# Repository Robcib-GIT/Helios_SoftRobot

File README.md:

**Helios SoftRobot**
=====================================

**Installation and Configuration**
-------------------------------

### Step 1: Clone the Helios repository

Clone the Helios repository using Git:

```bash
git clone https://github.com/JaimeBravoAlgaba/Helios_SoftRobot.git
```

### Step 2: Create a ROS2 workspace

Create a directory for the ROS2 workspace and make sure it's empty:

```bash
mkdir -p helios_ws/src
```

### Step 3: Install the helios_robot package in the workspace

Copy the helios_robot package to the ROS2 workspace:

```bash
cp -r Helios_SoftRobot/Código/helios_robot helios_ws/src
cd helios_ws/src
```

### Step 4: Install the micro_ros_setup package

Clone the micro_ros_setup repository and make sure it's on the branch corresponding to your ROS2 version:

```bash
git clone https://github.com/micro-ROS/micro_ros_setup.git -b $ROS_DISTRO
cd ..
```

### Step 5: Build the workspace

Update dependencies and build the ROS2 workspace:

```bash
rosdep update && rosdep install --from-paths src --ignore-src -y
colcon build --symlink-install
source install/local_setup.bash
```

### Step 6: Create a MicroROS agent

Create a MicroROS agent and configure the environment:

```bash
ros2 run micro_ros_setup create_agent_ws.sh
ros2 run micro_ros_setup build_agent.sh
source install/local_setup.sh
```

### Step 7: Connect to the ESP32 and run the agent

Change your IP address to 192.168.2.76:

Turn on the robot if you haven't already.

**Terminal Control**
-----------
- You can use the helios_robot.sh file to automatically launch the necessary nodes:
```bash
# Launches the MicroROS agent, kinematics and pose prediction
# In the folder where the file is located, run:
./helios_robot.sh
```
and immediately after, click the RESET button on the ESP32.

- Launch the visualization node:
```bash
ros2 run helios_robot helios_robot_plot
```

- Control the cable lengths, in meters:
```bash
# [L00, L01, L02, L03, L10, L11, ... L22, L23]
ros2 topic pub --once /helios_cables_cmd std_msgs/msg/Float32MultiArray "data: [0,0,0,0,  0,0,0,0,  0,0,0,0]"
```

- Send command in theta and phi coordinates, in radians:
```bash
# [th0, th1, th2, phi0, phi1, phi2]
ros2 topic pub --once /helios_sections_cmd std_msgs/msg/Float32MultiArray "data: [0,0,0,  0,0,0]"
```

- Control the tool (value from 0 to 255):
```bash
ros2 topic pub --once /helios_tool_cmd std_msgs/msg/Int8 "data: 127"
```

### Alternative: Connect to ESP32 via USB

You can use the Helios with a USB cable:
Connect the ESP32 to the USB port and upload the esp32 project after uncommenting the lines that allow serial connection in "main.cpp" and changing board_microros_transport to "serial" in the platformio.ini file

Run the MicroROS agent with:

```bash
ros2 run micro_ros_agent micro_ros_agent serial --dev /dev/ttyUSB0
```

### Common Error Resolution

If an error appears when connecting the ESP32, make sure to grant your user access to the ttyUSB0 USB port:

1. Check the user group that has access to the port:
```bash
stat /dev/ttyUSB0
```

It should show something like: "Gid: (   20/ dialout)"

2. Add your user to the "dialout" group or whichever group appeared:
```bash
sudo usermod -a -G dialout $USER
```
3. Grant read and write permissions to the port:
```bash
sudo chmod a+rw /dev/ttyUSB0
```

After resetting the ESP32, its topics should be visible from another terminal.

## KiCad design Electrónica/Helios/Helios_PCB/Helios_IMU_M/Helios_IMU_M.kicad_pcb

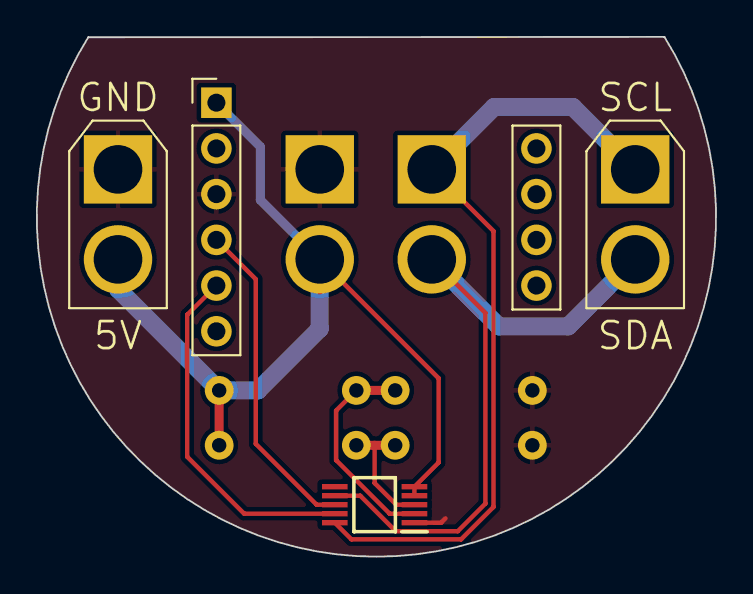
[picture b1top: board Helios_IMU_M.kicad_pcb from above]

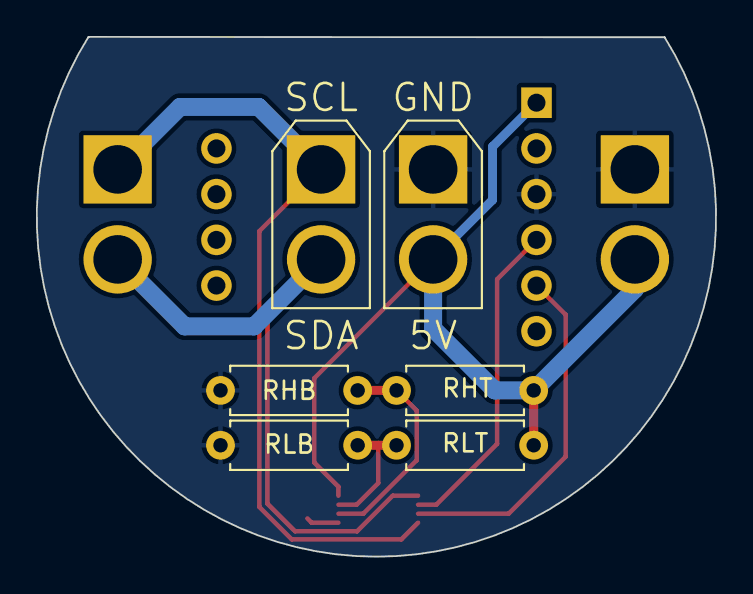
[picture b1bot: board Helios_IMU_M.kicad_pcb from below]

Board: 2 copper layers, 37.7 x 28.9 mm, 10 parts (6 on the bottom side), 8 nets.

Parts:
IMU1: BNO_055
J1, J2, J3, J4: Conn_01x02_Pin; XT30U-M_1x02_P5.0mm_Vertical
LTC4316: LTC4316CMS#PBF; SOP50P490X110-10N
RHB: R; R_Axial_DIN0207_L6.3mm_D2.5mm_P7.62mm_Horizontal
RHT: R; R_Axial_DIN0207_L6.3mm_D2.5mm_P7.62mm_Horizontal
RLB: R; R_Axial_DIN0207_L6.3mm_D2.5mm_P7.62mm_Horizontal
RLT: R; R_Axial_DIN0207_L6.3mm_D2.5mm_P7.62mm_Horizontal

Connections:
GND: IMU1.3 (GND), J1.1, J3.1, LTC4316.1 (GND), RHB.2, RLB.2
SCL: J2.1, J4.1, LTC4316.10 (SCLIN)
SCL_OUT: IMU1.5 (SCL), LTC4316.9 (SCLOUT)
SDA: J2.2, J4.2, LTC4316.7 (SDAIN)
SDA_OUT: IMU1.4 (SDA), LTC4316.8 (SDAOUT)
VCC: IMU1.1 (Vin), J1.2, J3.2, LTC4316.4 (VCC), LTC4316.5 (ENABLE), RHT.1, RLT.1
XORH: LTC4316.2 (XORH), RHB.1, RHT.2
XORL: LTC4316.3 (XORL), RLB.1, RLT.2

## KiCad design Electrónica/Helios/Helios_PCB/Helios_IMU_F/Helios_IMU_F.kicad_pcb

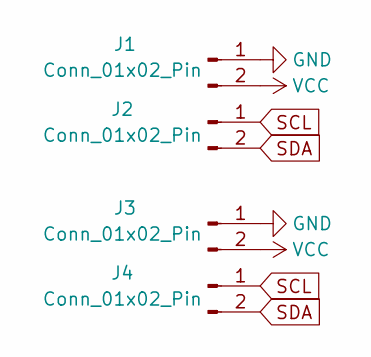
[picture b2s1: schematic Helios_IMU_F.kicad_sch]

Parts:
J1, J2, J3, J4: Conn_01x02_Pin; XT30U-M_1x02_P5.0mm_Vertical

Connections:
GND: J1.1, J3.1
SCL: J2.1, J4.1
SDA: J2.2, J4.2
VCC: J1.2, J3.2

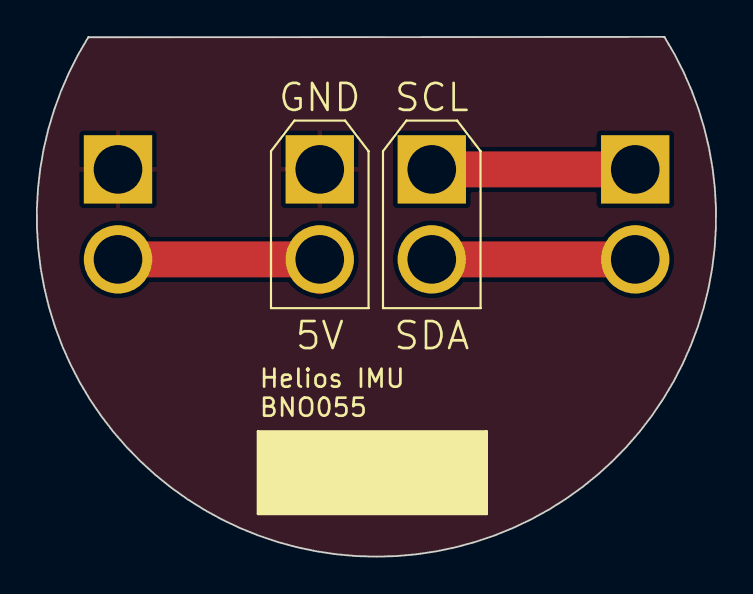
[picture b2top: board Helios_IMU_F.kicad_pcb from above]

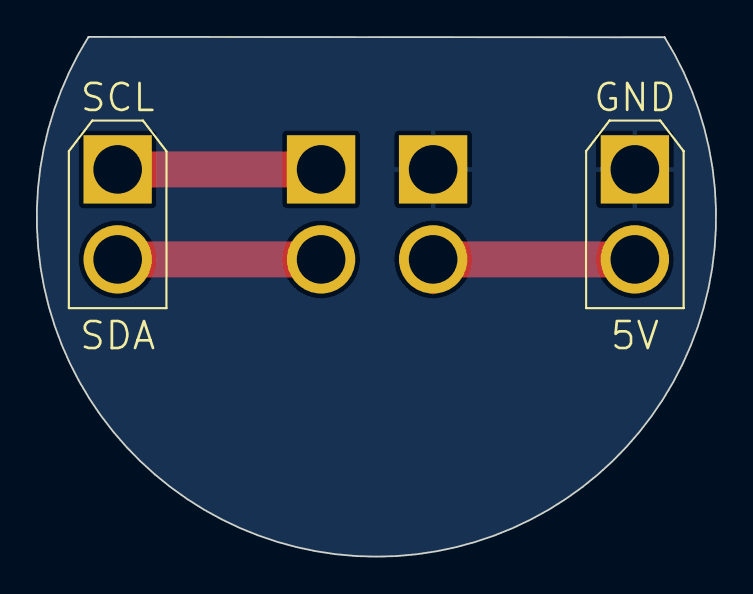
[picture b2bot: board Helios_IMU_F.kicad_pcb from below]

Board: 2 copper layers, 37.7 x 28.9 mm, 4 parts (2 on the bottom side), 4 nets.

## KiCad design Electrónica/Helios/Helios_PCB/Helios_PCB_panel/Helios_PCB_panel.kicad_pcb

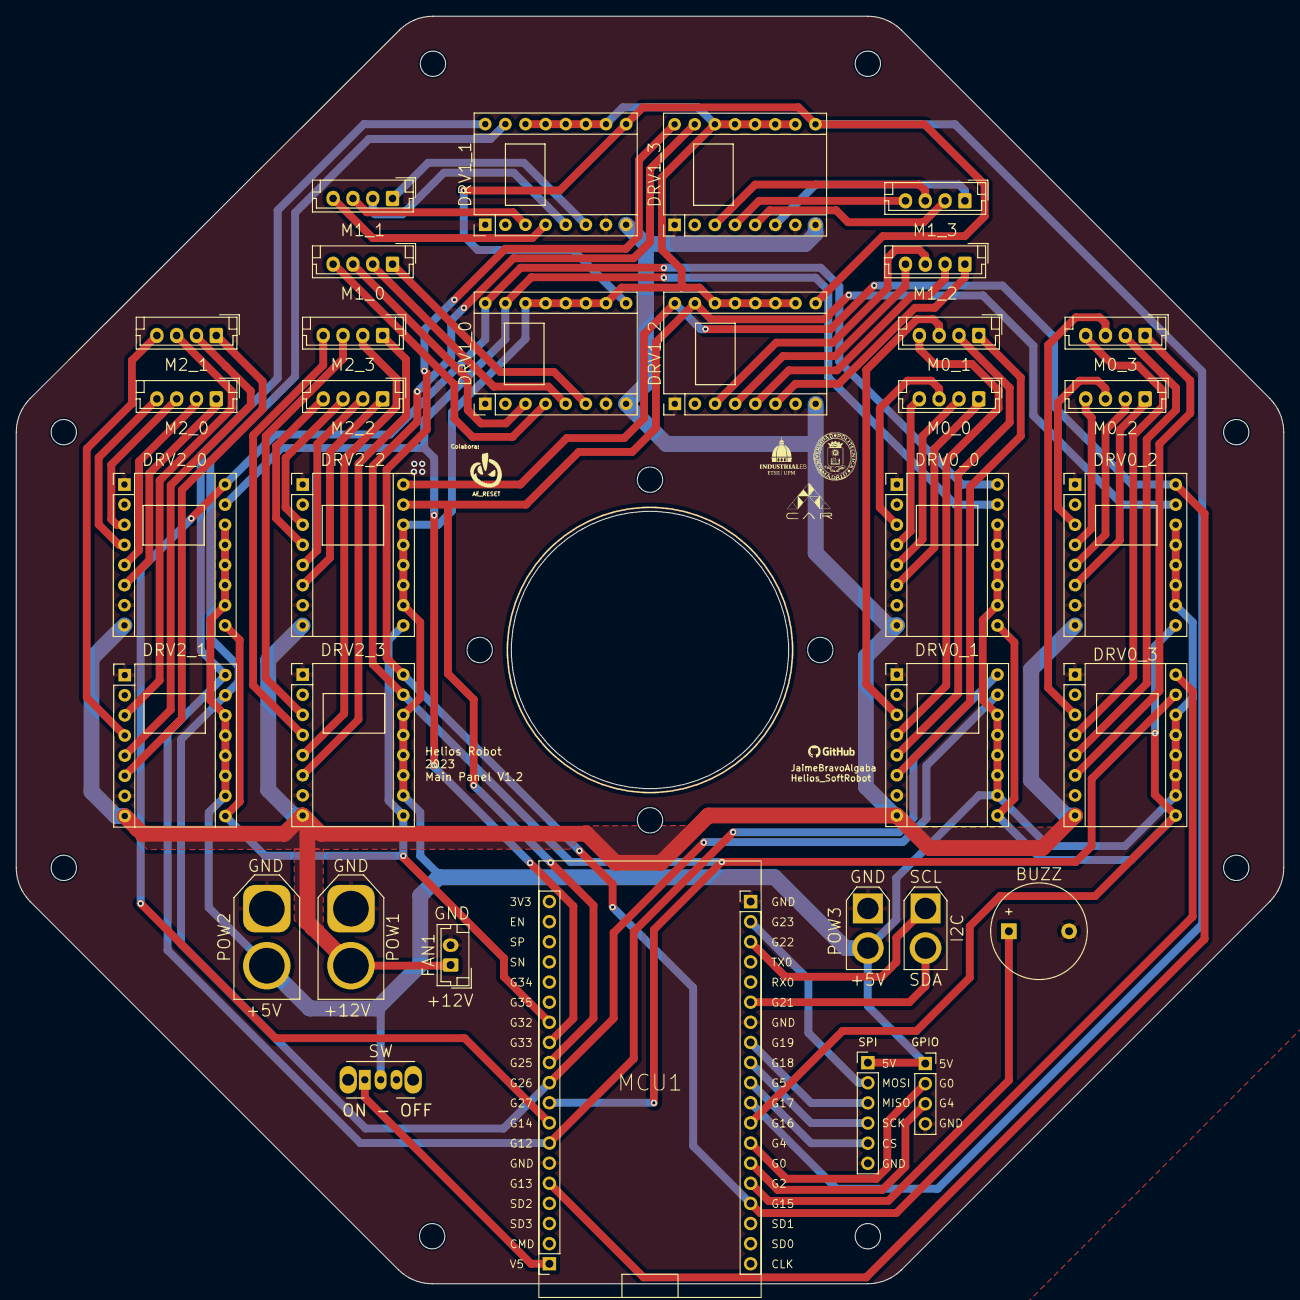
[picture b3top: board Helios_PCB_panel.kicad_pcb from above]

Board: 2 copper layers, 160.0 x 160.0 mm, 46 parts (0 on the bottom side), 72 nets.

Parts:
BUZZ: Buzzer; Buzzer_12x9.5RM7.6
DRV0_0, DRV0_1, DRV0_2, DRV0_3, DRV1_0, DRV1_1, DRV1_2, DRV1_3, DRV2_0, DRV2_1, DRV2_2, DRV2_3: Pololu_Breakout_DRV8825; Pololu_Breakout-16_15.2x20.3mm
FAN1: 12VDC; JST_EH_B2B-EH-A_1x02_P2.50mm_Vertical
GPIO: Conn_01x04_Pin; PinSocket_1x04_P2.54mm_Vertical
H1, H2, H3, H4, H5, H6, H7, H8, H9, H10, H11, H12: MountingHole; MountingHole_3.2mm_M3
I2C: I2C1; XT30U-F_1x02_P5.0mm_Vertical
M0_0, M0_1, M0_2, M0_3, M1_0, M1_1, M1_2, M1_3, M2_0, M2_1, M2_2, M2_3: Conn_01x04_Pin; JST_EH_B4B-EH-A_1x04_P2.50mm_Vertical
MCU1: NodeMCU
POW1: 12VDC; XT60-M_1x02_P7.20mm_Vertical
POW2: 5VDC; XT60-M_1x02_P7.20mm_Vertical
POW3: 5VDC; XT30U-F_1x02_P5.0mm_Vertical
SPI: Conn_01x06_Pin; PinHeader_1x06_P2.54mm_Vertical
SW: SW_SPDT; SW_CuK_OS102011MA1QN1_SPDT_Angled

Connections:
+5V: DRV0_0.10 (M0), DRV0_0.11 (M1), DRV0_0.12 (M2), DRV0_0.13 (~RST), DRV0_0.14 (~SLP), DRV0_1.10 (M0), DRV0_1.11 (M1), DRV0_1.12 (M2), DRV0_1.13 (~RST), DRV0_1.14 (~SLP), DRV0_2.10 (M0), DRV0_2.11 (M1), DRV0_2.12 (M2), DRV0_2.13 (~RST), DRV0_2.14 (~SLP), DRV0_3.10 (M0), DRV0_3.11 (M1), DRV0_3.12 (M2), DRV0_3.13 (~RST), DRV0_3.14 (~SLP), DRV1_0.10 (M0), DRV1_0.11 (M1), DRV1_0.12 (M2), DRV1_0.13 (~RST), DRV1_0.14 (~SLP), DRV1_1.10 (M0), DRV1_1.11 (M1), DRV1_1.12 (M2), DRV1_1.13 (~RST), DRV1_1.14 (~SLP), DRV1_2.10 (M0), DRV1_2.11 (M1), DRV1_2.12 (M2), DRV1_2.13 (~RST), DRV1_2.14 (~SLP), DRV1_3.10 (M0), DRV1_3.11 (M1), DRV1_3.12 (M2), DRV1_3.13 (~RST), DRV1_3.14 (~SLP), DRV2_0.10 (M0), DRV2_0.11 (M1), DRV2_0.12 (M2), DRV2_0.13 (~RST), DRV2_0.14 (~SLP), DRV2_1.10 (M0), DRV2_1.11 (M1), DRV2_1.12 (M2), DRV2_1.13 (~RST), DRV2_1.14 (~SLP), DRV2_2.10 (M0), DRV2_2.11 (M1), DRV2_2.12 (M2), DRV2_2.13 (~RST), DRV2_2.14 (~SLP), DRV2_3.10 (M0), DRV2_3.11 (M1), DRV2_3.12 (M2), DRV2_3.13 (~RST), DRV2_3.14 (~SLP), GPIO.1, POW2.2, POW3.2, SPI.1, SW.2 (B)
+12V: DRV0_0.8 (VMOT), DRV0_1.8 (VMOT), DRV0_2.8 (VMOT), DRV0_3.8 (VMOT), DRV1_0.8 (VMOT), DRV1_1.8 (VMOT), DRV1_2.8 (VMOT), DRV1_3.8 (VMOT), DRV2_0.8 (VMOT), DRV2_1.8 (VMOT), DRV2_2.8 (VMOT), DRV2_3.8 (VMOT), FAN1.1, POW1.2
BUZZ: BUZZ.1 (-), MCU1.24 (G2)
CS: MCU1.29 (G5), SPI.5
D0: DRV0_0.16 (DIR), DRV1_0.16 (DIR), DRV2_0.16 (DIR), MCU1.12 (G14)
D1: DRV0_1.16 (DIR), DRV1_1.16 (DIR), DRV2_1.16 (DIR), MCU1.13 (G12)
D2: DRV0_2.16 (DIR), DRV1_2.16 (DIR), DRV2_2.16 (DIR), MCU1.15 (G13)
D3: DRV0_3.16 (DIR), DRV1_3.16 (DIR), DRV2_3.16 (DIR), MCU1.23 (G15)
EN0: DRV0_0.9 (~EN), DRV0_1.9 (~EN), DRV0_2.9 (~EN), DRV0_3.9 (~EN), MCU1.27 (G16)
EN1: DRV1_0.9 (~EN), DRV1_1.9 (~EN), DRV1_2.9 (~EN), DRV1_3.9 (~EN), MCU1.28 (G17)
EN2: DRV2_0.9 (~EN), DRV2_1.9 (~EN), DRV2_2.9 (~EN), DRV2_3.9 (~EN), MCU1.7 (G32)
GND: BUZZ.2 (+), DRV0_0.1 (GND), DRV0_0.7 (GND), DRV0_1.1 (GND), DRV0_1.7 (GND), DRV0_2.1 (GND), DRV0_2.7 (GND), DRV0_3.1 (GND), DRV0_3.7 (GND), DRV1_0.1 (GND), DRV1_0.7 (GND), DRV1_1.1 (GND), DRV1_1.7 (GND), DRV1_2.1 (GND), DRV1_2.7 (GND), DRV1_3.1 (GND), DRV1_3.7 (GND), DRV2_0.1 (GND), DRV2_0.7 (GND), DRV2_1.1 (GND), DRV2_1.7 (GND), DRV2_2.1 (GND), DRV2_2.7 (GND), DRV2_3.1 (GND), DRV2_3.7 (GND), FAN1.2, GPIO.4, MCU1.14 (GND), MCU1.32 (GND), MCU1.38 (GND), POW1.1, POW2.1, POW3.1, SPI.6
MISO: MCU1.31 (G19), SPI.3
MOSI: MCU1.37 (G23), SPI.2
unnamed: DRV0_0.4 (A1), M0_0.4
unnamed: DRV0_0.3 (A2), M0_0.3
unnamed: DRV0_0.5 (B1), M0_0.2
unnamed: DRV0_0.6 (B2), M0_0.1
unnamed: DRV0_1.4 (A1), M0_1.4
unnamed: DRV0_1.3 (A2), M0_1.3
unnamed: DRV0_1.5 (B1), M0_1.2
unnamed: DRV0_1.6 (B2), M0_1.1
unnamed: DRV0_2.4 (A1), M0_2.4
unnamed: DRV0_2.3 (A2), M0_2.3
unnamed: DRV0_2.5 (B1), M0_2.2
unnamed: DRV0_2.6 (B2), M0_2.1
unnamed: DRV0_3.4 (A1), M0_3.4
unnamed: DRV0_3.3 (A2), M0_3.3
unnamed: DRV0_3.5 (B1), M0_3.2
unnamed: DRV0_3.6 (B2), M0_3.1
unnamed: DRV1_0.4 (A1), M1_0.4
unnamed: DRV1_0.3 (A2), M1_0.3
unnamed: DRV1_0.5 (B1), M1_0.2
unnamed: DRV1_0.6 (B2), M1_0.1
unnamed: DRV1_1.4 (A1), M1_1.4
unnamed: DRV1_1.3 (A2), M1_1.3
unnamed: DRV1_1.5 (B1), M1_1.2
unnamed: DRV1_1.6 (B2), M1_1.1
unnamed: DRV1_2.4 (A1), M1_2.4
unnamed: DRV1_2.3 (A2), M1_2.3
unnamed: DRV1_2.5 (B1), M1_2.2
unnamed: DRV1_2.6 (B2), M1_2.1
unnamed: DRV1_3.4 (A1), M1_3.4
unnamed: DRV1_3.3 (A2), M1_3.3
unnamed: DRV1_3.5 (B1), M1_3.2
unnamed: DRV1_3.6 (B2), M1_3.1
unnamed: DRV2_0.4 (A1), M2_0.4
unnamed: DRV2_0.3 (A2), M2_0.3
unnamed: DRV2_0.5 (B1), M2_0.2
unnamed: DRV2_0.6 (B2), M2_0.1
unnamed: DRV2_1.4 (A1), M2_1.4
unnamed: DRV2_1.3 (A2), M2_1.3
unnamed: DRV2_1.5 (B1), M2_1.2
unnamed: DRV2_1.6 (B2), M2_1.1
unnamed: DRV2_2.4 (A1), M2_2.4
unnamed: DRV2_2.3 (A2), M2_2.3
unnamed: DRV2_2.5 (B1), M2_2.2
unnamed: DRV2_2.6 (B2), M2_2.1
unnamed: DRV2_3.4 (A1), M2_3.4
unnamed: DRV2_3.3 (A2), M2_3.3
unnamed: DRV2_3.5 (B1), M2_3.2
unnamed: DRV2_3.6 (B2), M2_3.1
unnamed: GPIO.2, MCU1.26 (G4)
unnamed: GPIO.3, MCU1.25 (G0)
unnamed: MCU1.19 (V5), SW.1 (A)
S0: DRV0_0.15 (STEP), DRV1_0.15 (STEP), DRV2_0.15 (STEP), MCU1.8 (G33)
S1: DRV0_1.15 (STEP), DRV1_1.15 (STEP), DRV2_1.15 (STEP), MCU1.10 (G26)
S2: DRV0_2.15 (STEP), DRV1_2.15 (STEP), DRV2_2.15 (STEP), MCU1.9 (G25)
S3: DRV0_3.15 (STEP), DRV1_3.15 (STEP), DRV2_3.15 (STEP), MCU1.11 (G27)
SCK: MCU1.30 (G18), SPI.4
SCL: I2C.1, MCU1.36 (G22)
SDA: I2C.2, MCU1.33 (G21)

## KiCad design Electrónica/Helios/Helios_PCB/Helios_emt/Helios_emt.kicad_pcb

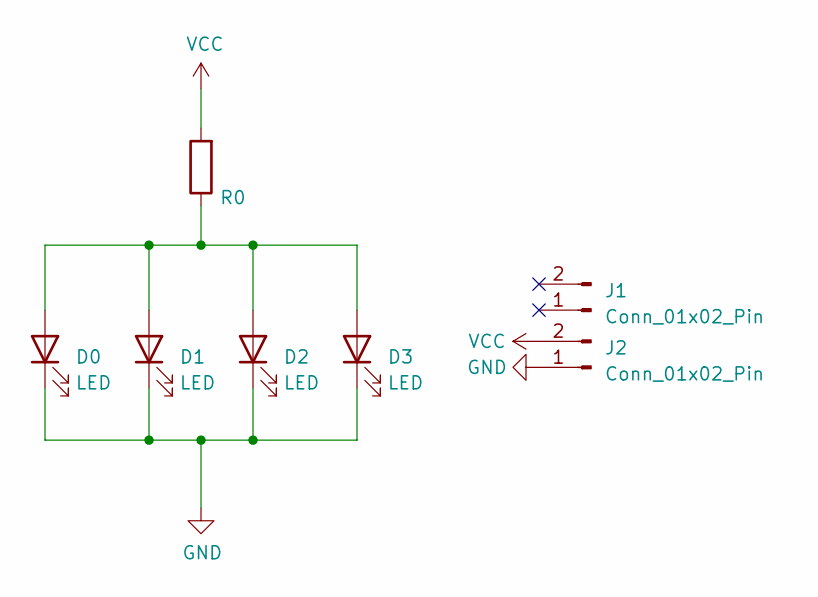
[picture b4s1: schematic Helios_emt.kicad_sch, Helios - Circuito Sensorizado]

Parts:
D0, D1, D2, D3: LED; LED_PLCC-2
J1, J2: Conn_01x02_Pin; AMASS_XT30U-F_1x02_P5.0mm_Vertical
R0: RL; R_0805_2012Metric

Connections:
GND: D0.1 (K), D1.1 (K), D2.1 (K), D3.1 (K), J2.1
unnamed: D0.2 (A), D1.2 (A), D2.2 (A), D3.2 (A), R0.1
VCC: J2.2, R0.2

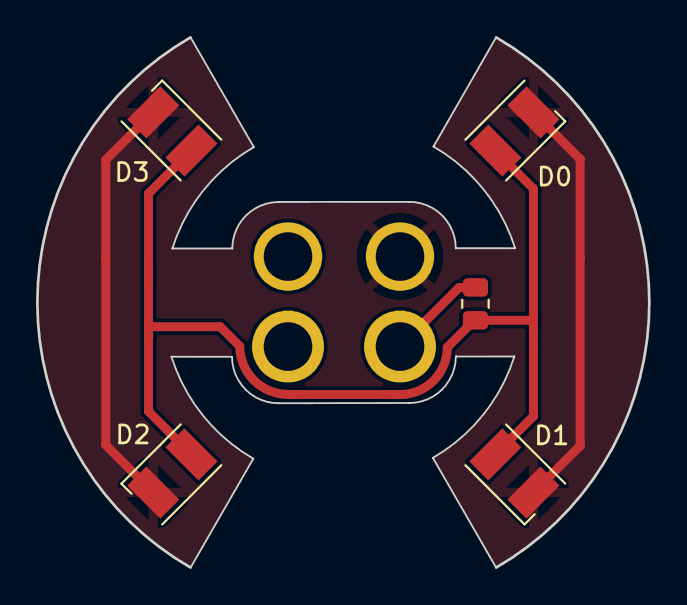
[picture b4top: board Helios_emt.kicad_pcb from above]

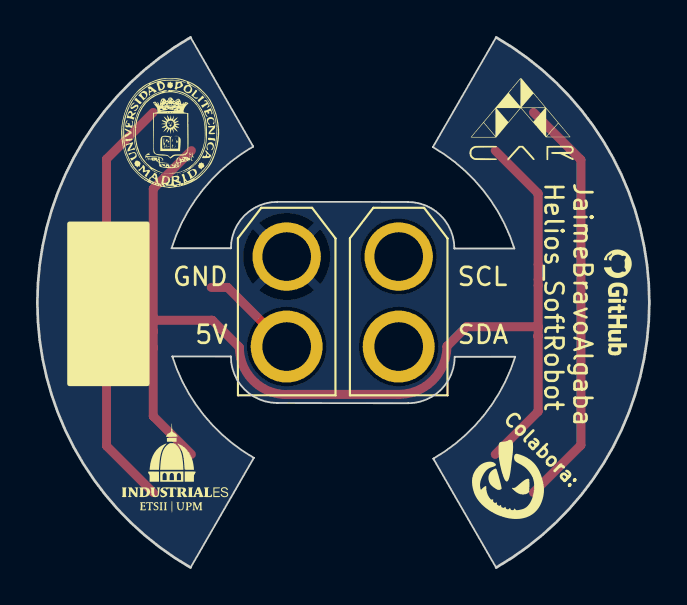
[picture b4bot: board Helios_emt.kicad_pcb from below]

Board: 2 copper layers, 34.0 x 29.5 mm, 7 parts (2 on the bottom side), 3 nets.

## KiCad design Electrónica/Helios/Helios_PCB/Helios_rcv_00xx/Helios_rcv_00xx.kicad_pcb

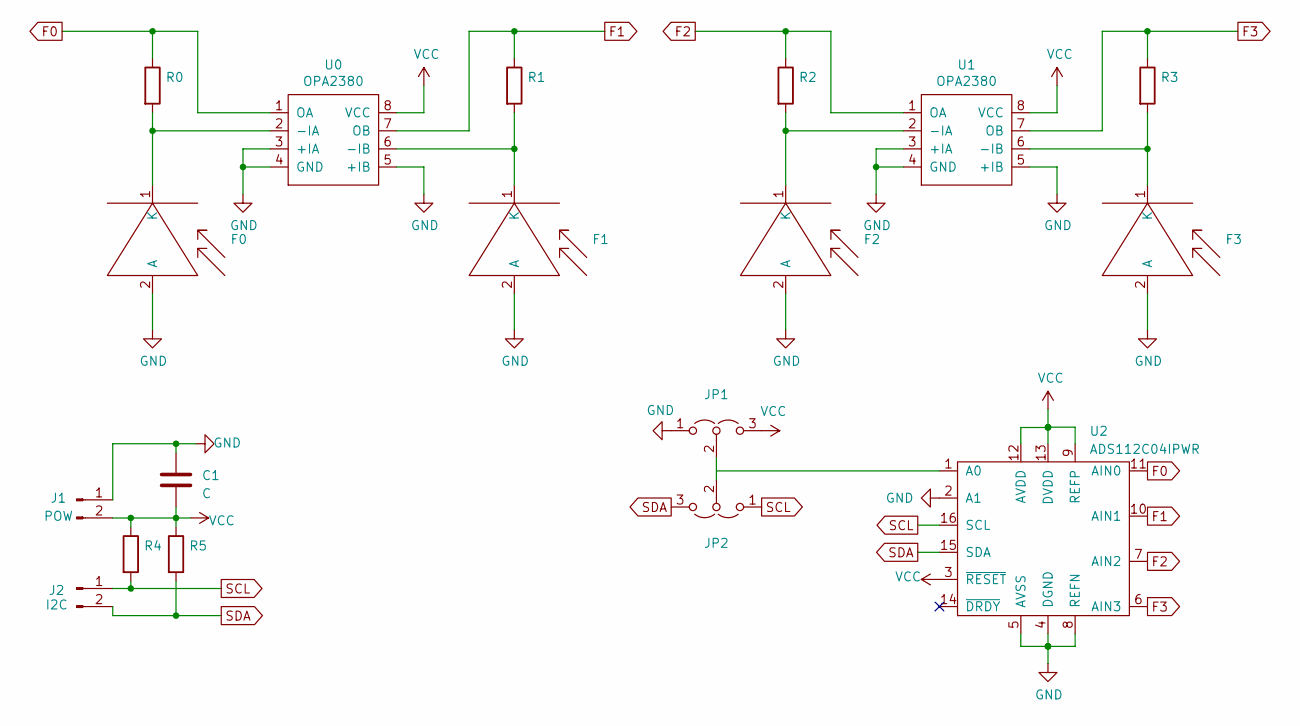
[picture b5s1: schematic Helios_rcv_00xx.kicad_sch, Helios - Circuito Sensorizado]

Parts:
C1: C; C_0805_2012Metric
F0, F1, F2, F3: SFH2704; SFH2704_Photodiode
J1: POW; XT30U-M_1x02_P5.0mm_Vertical
J2: I2C; XT30U-M_1x02_P5.0mm_Vertical
JP1, JP2: Jumper_3_Open; SolderJumper-3_P1.3mm_Open_Pad1.0x1.5mm
R0, R1, R2, R3, R4, R5: Rf; R_0805_2012Metric
U0, U1: OPA2380
U2: ADS112C04IPWR; TSSOP-16_4.4x5mm_P0.65mm

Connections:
F0: R0.1, U0.1 (OA), U2.11 (AIN0)
F1: R1.1, U0.7 (OB), U2.10 (AIN1)
F2: R2.1, U1.1 (OA), U2.7 (AIN2)
F3: R3.1, U1.7 (OB), U2.6 (AIN3)
GND: C1.1, F0.2 (A), F1.2 (A), F2.2 (A), F3.2 (A), J1.1, JP1.1 (A), U0.3 (+IA), U0.4 (GND), U0.5 (+IB), U1.3 (+IA), U1.4 (GND), U1.5 (+IB), U2.2 (A1), U2.4 (DGND), U2.5 (AVSS), U2.8 (REFN)
unnamed: F0.1 (K), R0.2, U0.2 (-IA)
unnamed: F1.1 (K), R1.2, U0.6 (-IB)
unnamed: F2.1 (K), R2.2, U1.2 (-IA)
unnamed: F3.1 (K), R3.2, U1.6 (-IB)
unnamed: JP1.2 (C), JP2.2 (C)
SCL: J2.1, JP2.1 (A), R4.2, U2.16 (SCL)
SDA: J2.2, JP2.3 (B), R5.2, U2.15 (SDA)
VCC: C1.2, J1.2, JP1.3 (B), R4.1, R5.1, U0.8 (VCC), U1.8 (VCC), U2.3 (~RESET), U2.9 (REFP), U2.12 (AVDD), U2.13 (DVDD)

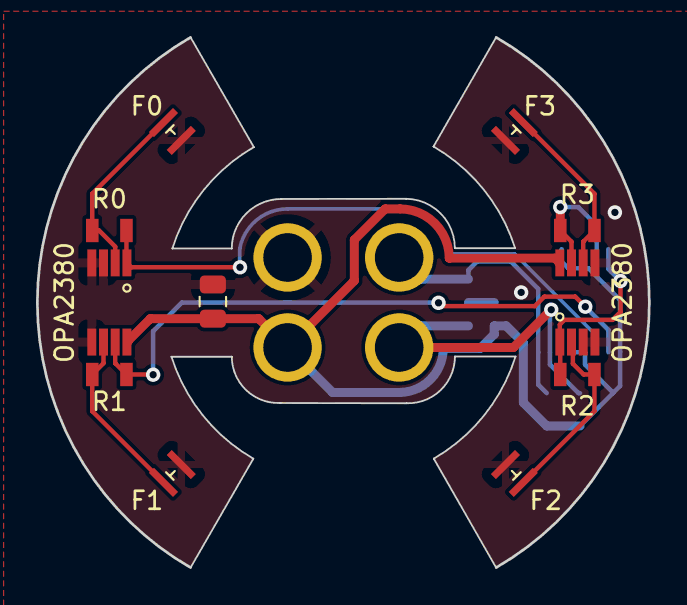
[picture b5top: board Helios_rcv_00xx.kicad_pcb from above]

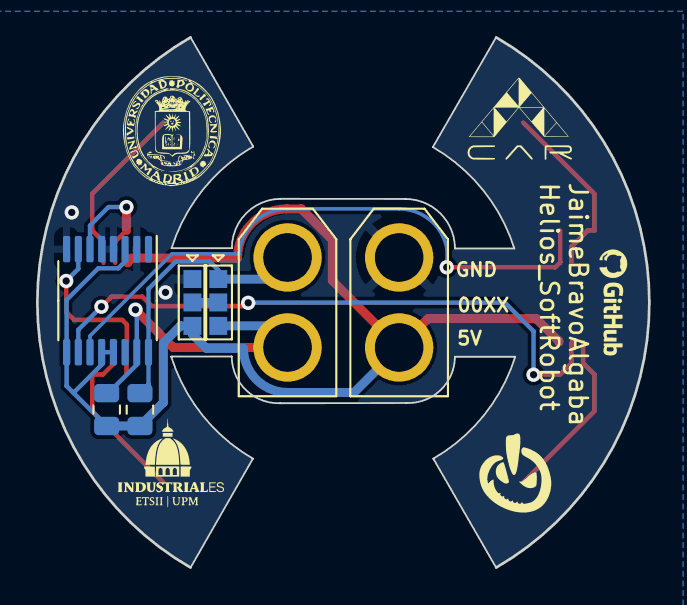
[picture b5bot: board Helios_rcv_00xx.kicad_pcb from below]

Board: 2 copper layers, 34.0 x 29.5 mm, 18 parts (7 on the bottom side), 13 nets.

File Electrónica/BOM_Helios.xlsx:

HELIOS MODULE - BOM |  |  |  |  |  |  | EMITTER PCBs |  |  |  | 20
 |  |  |  |  |  |  | RECEIVER PCBs |  |  |  | 20
COMPONENT | PCB | DESCRIPTION | DATASHEET | QTTY. PER CIRCUIT | QTTY. TOTAL | QTTY. PER ORDER | TO ORDER | ORDER PRICE | SHIPPING COSTS | TOTAL PRICE | LINK
OPA2380 | RECEIVER | Transimpedance Amplifier | opa2380 | 2 | 40 | 10 | 4 | 12.77 | 0 | 51.08 | https://es.aliexpress.com/item/1005002651519658.html?spm=a2g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
SFH2704 | RECEIVER | Photodiode | sfh2704 | 4 | 80 | 20 | 4 | 29.119999999999997 |  | 116.47999999999999 | https://es.rs-online.com/web/p/circuitos-integrados-de-senso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
2M RESISTOR | RECEIVER | Sensing Resistance |  | 4 | 80 |  | 0 | 0 | 0
OA3400 | EMITTER | Logic Level Mosfet | oa3400 | 1 | 20 | 50 | 1 | 0.91 | 1.1000000000000001 | 2.0100000000000002 | https://es.aliexpress.com/item/1005004174298809.html?spm=a2g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
2K RESISTOR | EMITTER | Pulldown Resistance |  | 1 | 20 |  | 0 | 0 | 0 | 0
241 RESISTOR | EMITTER | Current Limiting Resistance |  | 1 | 20 |  | 0 | 0 | 0 | 0

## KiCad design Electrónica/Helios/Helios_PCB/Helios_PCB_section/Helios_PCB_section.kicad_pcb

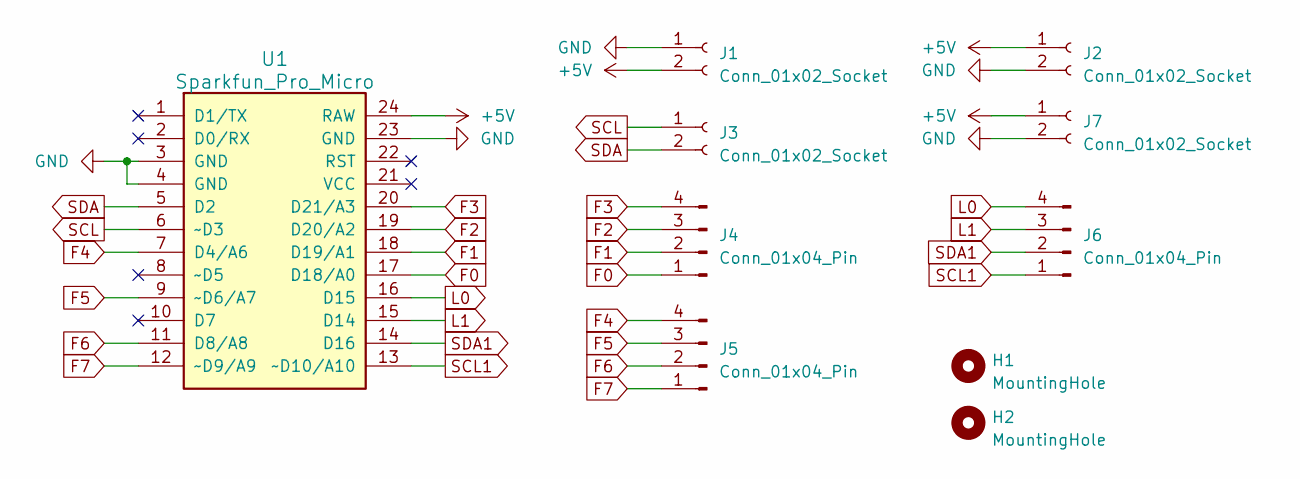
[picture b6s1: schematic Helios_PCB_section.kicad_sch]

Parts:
H1, H2: MountingHole; MountingHole_2.2mm_M2
J1, J3: Conn_01x02_Socket; XT30U-M_1x02_P5.0mm_Vertical
J2, J7: Conn_01x02_Socket; PinHeader_1x02_P2.54mm_Vertical
J4, J5, J6: Conn_01x04_Pin; PinHeader_1x04_P2.54mm_Vertical
U1: Sparkfun_Pro_Micro

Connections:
+5V: J1.2, J2.1, J7.1, U1.24 (RAW)
F0: J4.1, U1.17 (D18/A0)
F1: J4.2, U1.18 (D19/A1)
F2: J4.3, U1.19 (D20/A2)
F3: J4.4, U1.20 (D21/A3)
F4: J5.4, U1.7 (D4/A6)
F5: J5.3, U1.9 (~D6/A7)
F6: J5.2, U1.11 (D8/A8)
F7: J5.1, U1.12 (~D9/A9)
GND: J1.1, J2.2, J7.2, U1.3 (GND), U1.4 (GND), U1.23 (GND)
L0: J6.4, U1.16 (D15)
L1: J6.3, U1.15 (D14)
SCL: J3.1, U1.6 (~D3)
SCL1: J6.1, U1.13 (~D10/A10)
SDA: J3.2, U1.5 (D2)
SDA1: J6.2, U1.14 (D16)

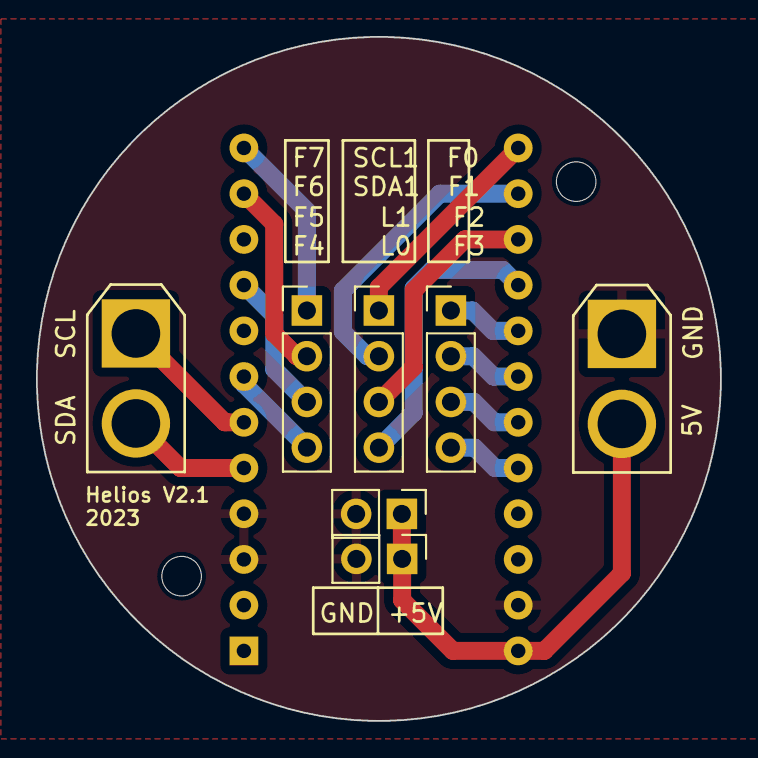
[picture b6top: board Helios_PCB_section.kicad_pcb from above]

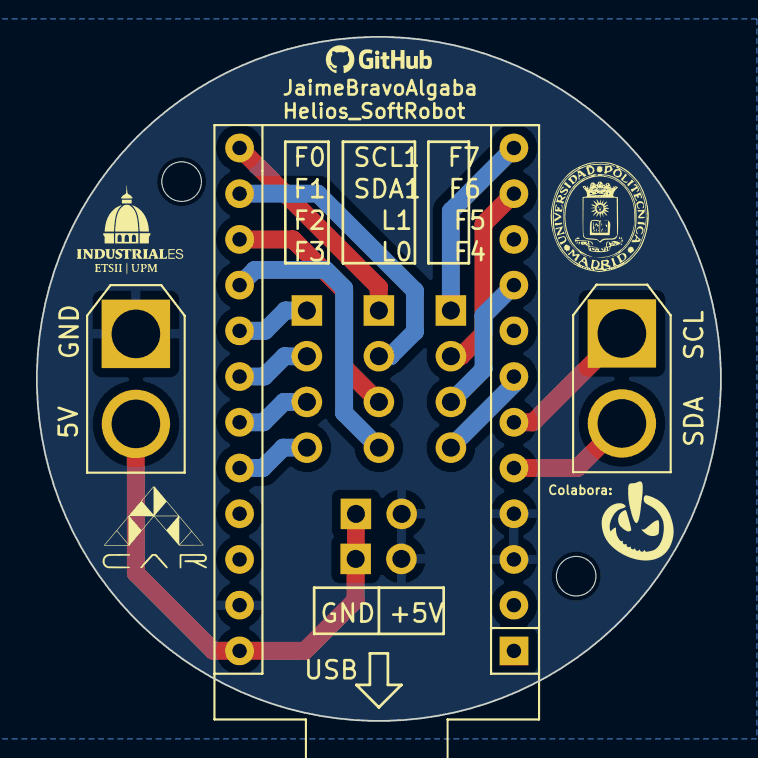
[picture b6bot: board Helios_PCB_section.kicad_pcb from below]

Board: 2 copper layers, 38.0 x 38.0 mm, 10 parts (3 on the bottom side), 16 nets.

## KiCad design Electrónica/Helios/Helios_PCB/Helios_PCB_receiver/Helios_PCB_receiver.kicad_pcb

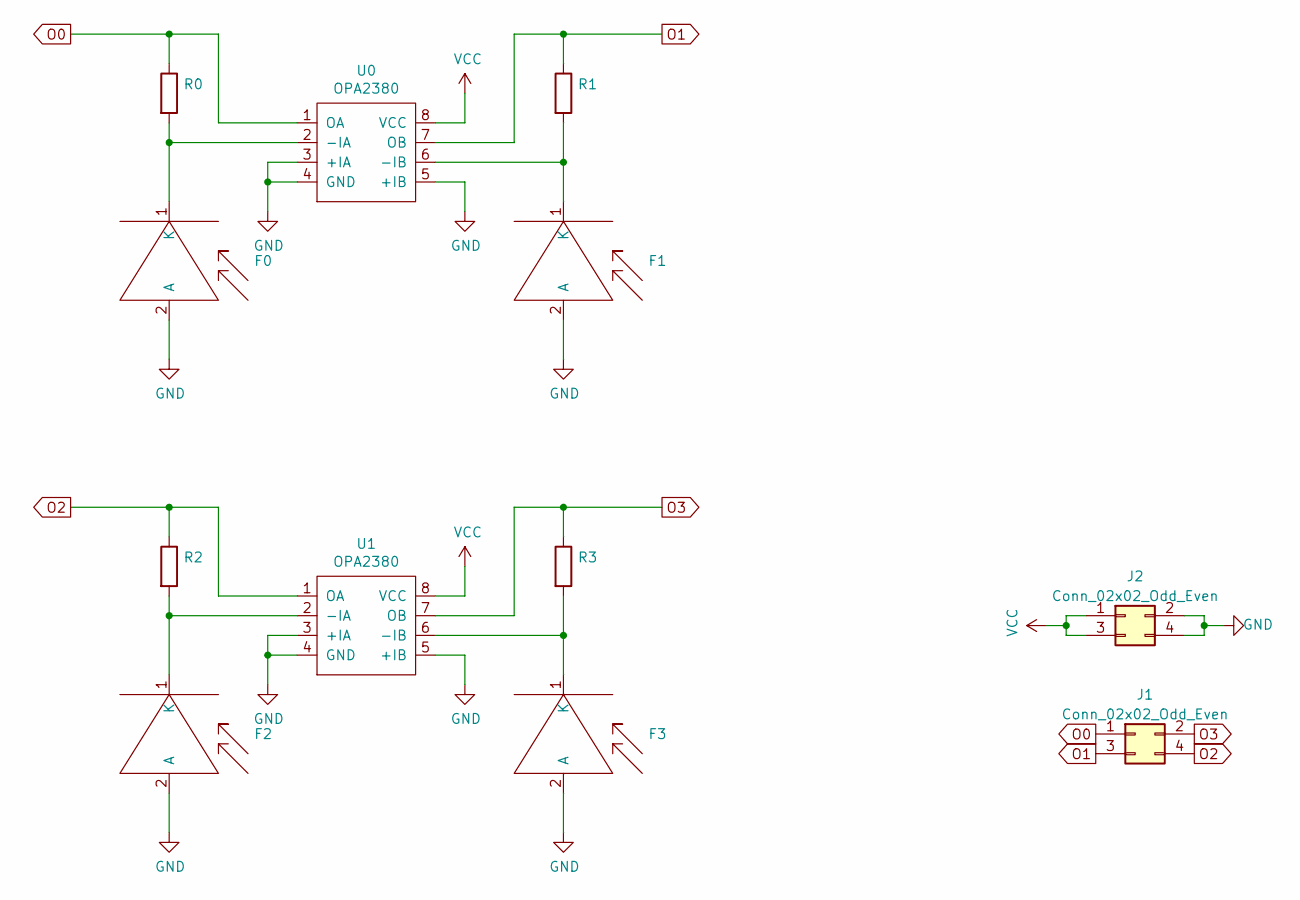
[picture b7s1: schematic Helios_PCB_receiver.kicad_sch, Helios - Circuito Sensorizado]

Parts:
F0, F1, F2, F3: SFH2704; SFH2704_Photodiode
J1, J2: Conn_02x02_Odd_Even; PinHeader_2x02_P2.54mm_Vertical
R0, R1, R2, R3: Rf; RS_0805
U0, U1: OPA2380

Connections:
GND: F0.2 (A), F1.2 (A), F2.2 (A), F3.2 (A), J2.2, J2.4, U0.3 (+IA), U0.4 (GND), U0.5 (+IB), U1.3 (+IA), U1.4 (GND), U1.5 (+IB)
unnamed: F0.1 (K), R0.2, U0.2 (-IA)
unnamed: F1.1 (K), R1.2, U0.6 (-IB)
unnamed: F2.1 (K), R2.2, U1.2 (-IA)
unnamed: F3.1 (K), R3.2, U1.6 (-IB)
O0: J1.1, R0.1, U0.1 (OA)
O1: J1.3, R1.1, U0.7 (OB)
O2: J1.4, R2.1, U1.1 (OA)
O3: J1.2, R3.1, U1.7 (OB)
VCC: J2.1, J2.3, U0.8 (VCC), U1.8 (VCC)

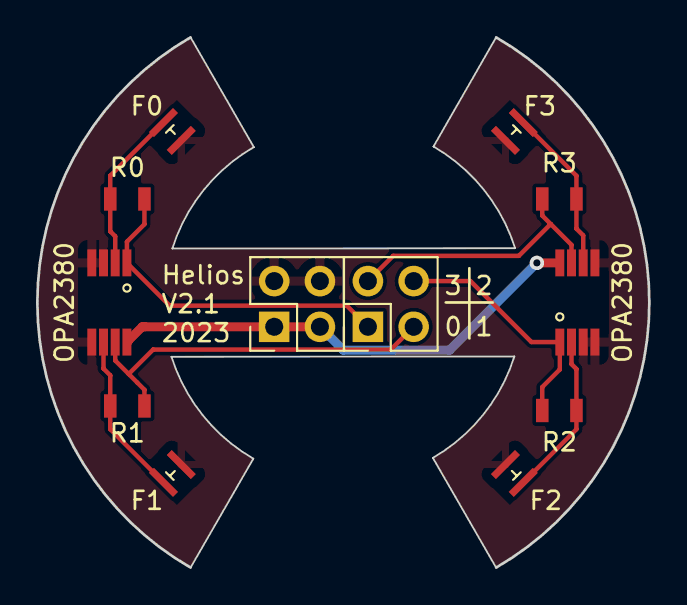
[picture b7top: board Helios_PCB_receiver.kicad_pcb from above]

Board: 2 copper layers, 34.0 x 29.5 mm, 12 parts (0 on the bottom side), 10 nets.

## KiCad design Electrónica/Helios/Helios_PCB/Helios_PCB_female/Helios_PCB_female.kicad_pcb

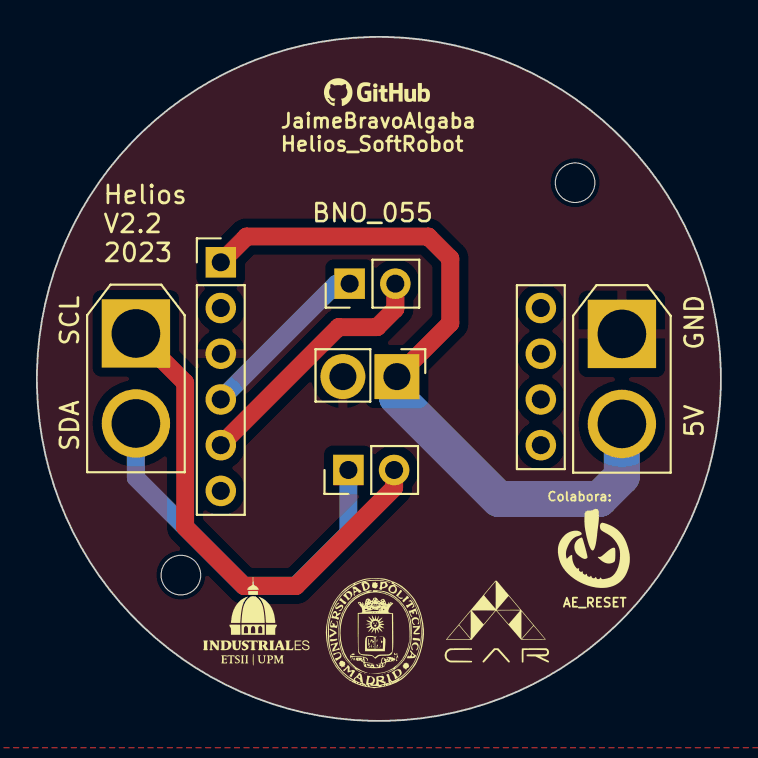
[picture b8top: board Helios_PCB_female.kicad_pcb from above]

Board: 2 copper layers, 38.0 x 38.0 mm, 8 parts (0 on the bottom side), 6 nets.

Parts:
BNO_055: BNO_055
H1, H2: MountingHole; MountingHole_2.2mm_M2
J1, J3: Conn_01x02_Socket; XT30U-M_1x02_P5.0mm_Vertical
J2, J4, J7: Conn_01x02_Socket; PinHeader_1x02_P2.54mm_Vertical

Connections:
+5V: BNO_055.1 (Vin), J1.2, J2.1
GND: BNO_055.3 (GND), J1.1, J2.2
SCL: J3.1, J7.2
SCL1: BNO_055.5 (SCL), J4.2
SDA: J3.2, J7.1
SDA1: BNO_055.4 (SDA), J4.1

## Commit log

2022-05-20 Included Initial Tests' files.
2022-05-20 Included new folders.
2022-05-20 Bibliografía Sof Robotics
2022-05-20 Bibliografía Soft Robotics
2022-05-20 Reestructuración. Vídeos Youtube.
2022-05-22 Receptor_I-075-4O
2022-05-23 Diseño PCB I_075
2022-06-05 Datasheet OPA2380 - Amplificador Operacional de Transimpedancia
2022-07-19 Pruebas WaveGuides
2022-07-25 Añadidos planos PCB Helios/ Reorganización carpetas
2022-07-25 Helios PCB - Schematic
2022-07-25 Helios -Sch Update
2022-07-25 Helios - Added Connectors
2022-08-03 Helios: VCC routing
2022-08-03 Helios: Top Layer
2022-08-03 Helios: Top Render
2022-08-05 Helios: Bot Layer Sch. (LEDs)
2022-08-07 Revert "Helios: Top Render"
    This reverts commit 206ce79916107aa4c1409288f7781bb33e41dd7b.
2022-08-07 Revert "Revert "Helios: Top Render""
    This reverts commit 9453b2ad7fff6b621a97970bf0e18bbf61baf802.
2022-08-07 Helios: Bot added resistance
2022-08-07 Revert "Helios: Bot added resistance"
    This reverts commit fc6911670fedaa5f37ce7a3614e7124a21ec9f54.
2022-08-07 Revert "Helios: Bot Layer Sch. (LEDs)"
    This reverts commit 9546d183d49721b4727ebea9dfcca252323cf9d1.
2022-08-07 Revert "Revert "Helios: Bot Layer Sch. (LEDs)""
    This reverts commit 1c39eb4d32ef048d6ab329c7f2d04810a34aa3c7.
2022-08-07 Revert "Revert "Helios: Bot added resistance""
    This reverts commit c4107a20008b53f7fb3aaff954cae4714a0471ec.
2022-08-07 Helios: arreglados errores plano de tierra
2022-08-07 Helios: Rev 1
2022-08-08 Helios: Second Iteration (half pcb)
2022-08-09 Helios: pcb 3dModel (draft)+Render
2022-09-16 Helios: Secnd iteration_Flex
2022-09-16 Helios: Second Iter
2022-09-18 Helios: Iteration3
2022-09-18 Logo
2022-09-18 Helios: Receiver V1.3
2022-09-18 Helios: Emitter V1.3
2022-09-18 Helios: Updated Silkscreen
2022-09-18 Helios: Updated Render
2022-09-19 Helios: Flex Update
2022-09-29 Helios: BOM
2022-10-08 Last changes V1.3
2022-10-08 Updated render
2022-10-29 29/10/2022
2022-10-29 Second version of Disk_A
2022-11-20 Modelo 3D Banco de Pruebas
2022-11-23 Helios_Section: added SPI Slave example
2022-11-25 Helios Section: Byte-Command Reception
2023-03-13 SPI comms
2023-04-16 Helios Test Board code update
2023-04-16 HeliosSensor class
2023-04-16 ContinuumSection class
2023-04-16 Actuator class
2023-04-16 Sensor Print method
2023-04-17 Update 17/04/2023
2023-07-26 SPI version
2023-07-26 I2C STABLE VERSION
2023-07-30 Implemented synchronous motion
2023-08-01 Implemented move feature.
2023-08-01 Added some macros and shortcuts
2023-08-01 Added init method for ActuatorBench
2023-08-01 Embeded HeliosSensor class into ContinuumSection
2023-08-01 Added enable() and disable functions for aactuator
2023-10-14 Minor Updates
2023-11-02 Disk_SM
2023-11-04 Added IMU fucntionality for MPU6050 module
2023-11-06 Added IMU PCB, female connection 3d model, assemblies. Error detected: invert connectors in PCB Male
2023-11-14 Helios Panel
2023-11-14 Minor changes
2023-11-14 PCBs ready for manufacturing
2023-11-20 V2.2 - BNO_055 IMU
2023-11-22 Updated Panel Pinout
2023-11-26 Added alluminium motor plate
2023-11-27 Updated Nema Pulley actuator
2023-11-28 Major changes: reverted Object Oriented Programming. Implemented multiple section control. PCB bug detected: GPIO34 & GPIO35.
2024-01-08 Generated STL files for pulley actuator
2024-01-28 Stable version
2024-01-29 Basic functionalities
2024-02-14 V3.0
2024-04-02 Pre MicroROS
2024-04-30 Module CHaracterization
2024-08-02 Added render
2024-08-03 Renders update
2024-08-04 Render explosionado
2024-08-05 Explosionado
2024-08-14 Helios Claw
2024-08-19 Reorganización Modelos3D
2024-08-19 Añadido archivo .sh
2024-08-20 Instrucciones de Instalación MicroROS
2024-08-21 Actualizadas instrucciones de instalación
2024-08-22 Modo de lectura continuo
2024-08-24 Calibración y mejoras IA
2024-08-26 IA reentrenada
2024-08-27 Updated sensor reading
2024-08-27 Bug arreglado
2024-08-27 Versión estable
2024-08-29 Actualización de los modelos de IA
2024-08-30 Actualizados modelos polinomiales
2024-08-30 IA reetrenada - entrada diferencial
2024-08-30 Actualizado script de análisis
2024-09-03 Fotos pruebas
2024-09-05 Pruebas de funcionamiento
2024-09-05 Añadidas instrucciones de instalación
2024-12-02 IMU Scan
2024-12-02 Setup con TOF
2024-12-06 Caracterización con TOFs
2024-12-06 Update W
2024-12-06 Reestructuración del código
2024-12-10 Processing and filtering of TOF data
2024-12-10 Test data
2024-12-10 New training
2024-12-11 Implementing control via Serial
2024-12-13 Closed-loop control
2024-12-16 Intermediate points
2024-12-16 Intemediate points corrected
2024-12-16 Minor bug fixing
2024-12-18 Updated comms
2024-12-18 Testing control OK
2024-12-18 New lengths
2025-01-09 datos
2025-01-09 Remove brackets
2025-01-13 Trained model V3
2025-01-14 New figures
2025-01-14 Reorganizado el código
2025-01-14 MAE for each PCC Parameter
2025-01-15 All graphs with font size 25
2025-01-16 Figures minor corrections
2025-01-29 Change in the graph
2025-04-07 Añadido filtro de media a L
2025-04-30 Update proyecto ESP32 to use WiFi
2025-05-05 Remote agent connection
2025-06-03 nodes to plot sensors and calibrate
2025-06-09 launch PCC
2025-06-10 visualization PCC : helios_robot_plot_PCC
2025-06-24 added first version of reversed kinematic node and visual
2025-07-07 Inversed kinematic node (in helios_IK_3)
2025-07-21 first version reversed kinematic (to correct)
2025-07-29 last update code Mateo
2025-09-11 Add demo GIF to README
2025-10-30 Update README to simplify micro-ROS agent setup
    Removed instructions for starting micro_ros_agent manually.
2025-11-14 Readme translation to English
